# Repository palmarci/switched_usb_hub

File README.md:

# switched_usb_hub

a very cheap and basic switched usb 2.0 hub design based on:

- SL2.1A USB 4 way hub IC
- CH340C USB - serial adapter
- STM32F030F4Px microcontroller

the mcu talks with the PC over UART and toggles some FETs using GPIOs. nothing fancy.

original idea to use the SL2.1A: https://github.com/Hugoyhu/ZephyrHub/

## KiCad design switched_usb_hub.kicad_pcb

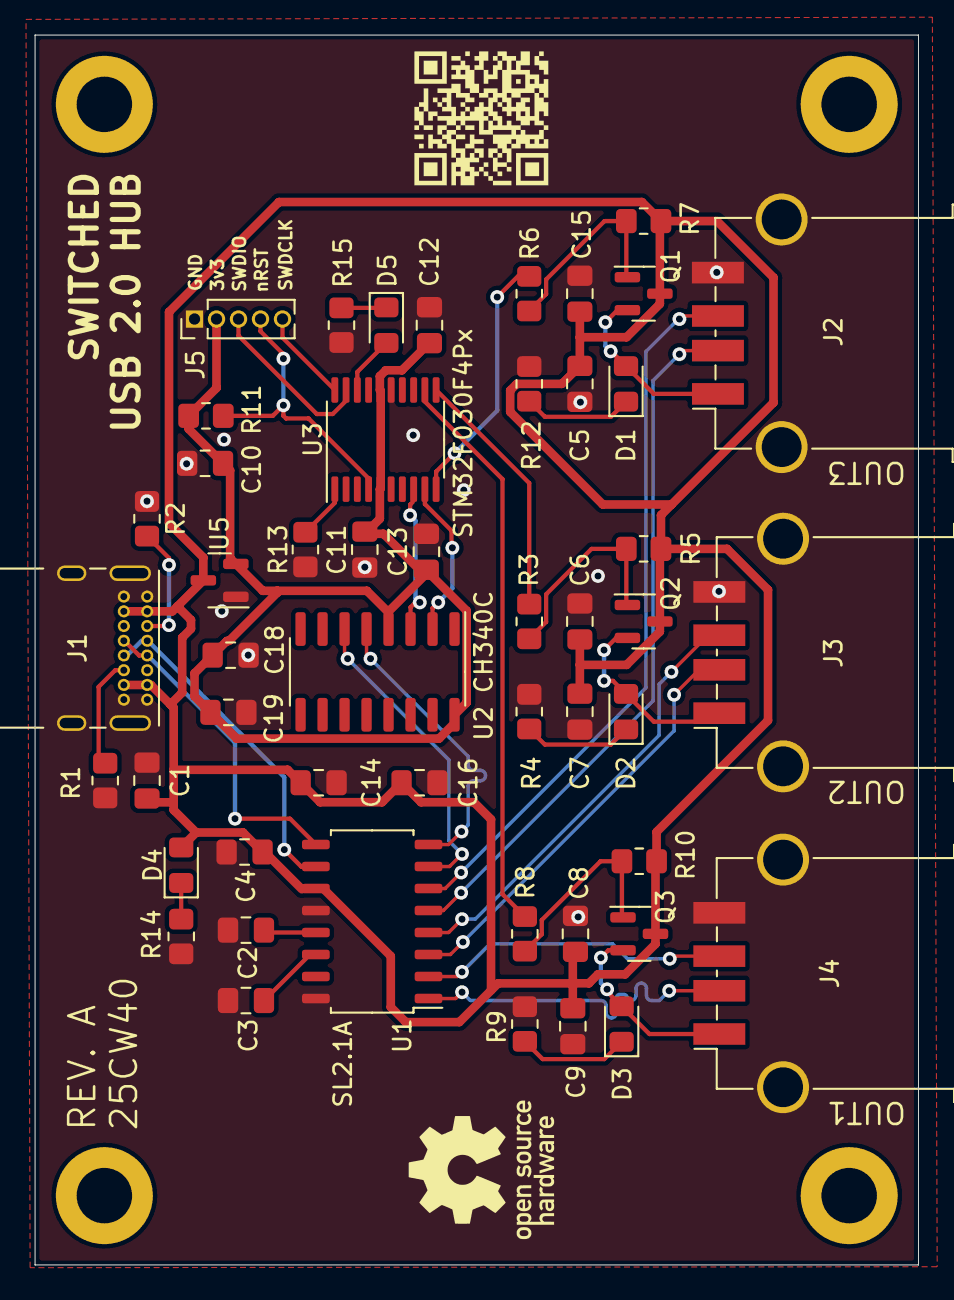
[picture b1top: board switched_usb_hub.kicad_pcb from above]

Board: 2 copper layers, 51.0 x 71.0 mm, 50 parts (0 on the bottom side), 38 nets.

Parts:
C1, C2, C3, C12, C14, C18: 10uF; C_0805_2012Metric_Pad1.18x1.45mm_HandSolder
C4, C6, C8, C10, C15, C16, C19: 100nF; C_0805_2012Metric_Pad1.18x1.45mm_HandSolder
C5, C7, C9, C11: 1uF; C_0805_2012Metric_Pad1.18x1.45mm_HandSolder
C13: 0.1uF; C_0805_2012Metric_Pad1.18x1.45mm_HandSolder
D1, D2, D3: LED; LED_0805_2012Metric_Pad1.15x1.40mm_HandSolder
D4: 5V IN; LED_0805_2012Metric_Pad1.15x1.40mm_HandSolder
D5: TEST LED; LED_0805_2012Metric_Pad1.15x1.40mm_HandSolder
J1: USB_C_Receptacle_USB2.0; USB_C_Receptacle_GCT_USB4085
J2, J3, J4: USB_A; USB_A_TE_292303-7_Horizontal
J5: JTAG_CONN; PinHeader_1x05_P1.27mm_Vertical
Q1, Q2, Q3: IRLML6402; SOT-23
R1, R2: 5.1K; R_0805_2012Metric_Pad1.20x1.40mm_HandSolder
R3, R6, R8: 100; R_0805_2012Metric_Pad1.20x1.40mm_HandSolder
R4, R9, R12, R14, R15: 330R; R_0805_2012Metric_Pad1.20x1.40mm_HandSolder
R5, R7, R10, R11, R13: 10k; R_0805_2012Metric_Pad1.20x1.40mm_HandSolder
U1: SL2.1A; SOIC-16_4.55x10.3mm_P1.27mm
U2: CH340C; SOIC-16_3.9x9.9mm_P1.27mm
U3: STM32F030F4Px; TSSOP-20_4.4x6.5mm_P0.65mm
U5: MCP1700x-330xxTT; SOT-23

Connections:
+3V3: C10.2, C11.2, C12.1, C13.1, C18.1, C19.1, J5.2 (VCC), R11.1, U2.4 (V3), U2.16 (VCC), U3.5 (VDDA), U3.16 (VDD), U5.2 (VO)
+5V: C1.1, C4.2, C5.1, C6.1, C7.1, C8.1, C9.1, C14.1, C15.1, C16.1, D4.2 (A), J1.A4 (VBUS), J1.A9 (VBUS), J1.B4 (VBUS), J1.B9 (VBUS), Q1.3 (D), Q2.3 (D), Q3.3 (D), R5.1, R7.1, R10.1, U1.11 (VCC5V), U5.3 (VI)
/D1+: U1.8 (DP1), U2.5 (UD+)
/D1-: U1.7 (DM1), U2.6 (UD-)
/D2+: J2.3 (D+), U1.6 (DP2)
/D2-: J2.2 (D-), U1.5 (DM2)
/D3+: J3.3 (D+), U1.4 (DP3)
/D3-: J3.2 (D-), U1.3 (DM3)
/D4+: J4.3 (D+), U1.2 (DP4)
/D4-: J4.2 (D-), U1.1 (DM4)
/mcu_subsys/PSU_SW0: R6.2, U3.10 (PA4)
/mcu_subsys/PSU_SW1: R3.2, U3.11 (PA5)
/mcu_subsys/PSU_SW2: R8.2, U3.12 (PA6)
GND: C1.2, C2.2, C3.1, C4.1, C5.2, C6.2, C7.2, C8.2, C9.2, C10.1, C11.1, C12.2, C13.2, C14.2, C15.2, C16.2, C18.2, C19.2, J1.A1 (GND), J1.A12 (GND), J1.B1 (GND), J1.B12 (GND), J1.S1 (SHIELD), J2.4 (GND), J2.5 (Shield), J3.4 (GND), J3.5 (Shield), J4.4 (GND), J4.5 (Shield), J5.1 (GND), R1.2, R2.1, R4.2, R9.2, R12.2, R13.1, R14.2, R15.2, U1.12 (GND), U1.16 (XIN), U3.15 (VSS), U5.1 (GND)
unnamed: C2.1, U1.13 (VDD3)
unnamed: C3.2, U1.14 (VDD18)
unnamed: D1.1 (K), R12.1
unnamed: D1.2 (A), J2.1 (VBUS), Q1.2 (S)
unnamed: D2.1 (K), R4.1
unnamed: D2.2 (A), J3.1 (VBUS), Q2.2 (S)
unnamed: D3.1 (K), R9.1
unnamed: D3.2 (A), J4.1 (VBUS), Q3.2 (S)
unnamed: D4.1 (K), R14.1
unnamed: D5.1 (K), R15.1
unnamed: D5.2 (A), U3.18 (PA10)
unnamed: J1.A5 (CC1), R2.2
unnamed: J1.A6 (D+), J1.B6 (D+), U1.10 (UDP)
unnamed: J1.A7 (D-), J1.B7 (D-), U1.9 (UDM)
unnamed: J1.B5 (CC2), R1.1
unnamed: J5.3 (SWDIO), U3.19 (PA13)
unnamed: J5.4 (nRST), R11.2, U3.4 (NRST)
unnamed: J5.5 (SWDCLK), U3.20 (PA14)
unnamed: Q1.1 (G), R6.1, R7.2
unnamed: Q2.1 (G), R3.1, R5.2
unnamed: Q3.1 (G), R8.1, R10.2
unnamed: R13.2, U3.1 (BOOT0)
unnamed: U2.2 (TXD), U3.9 (PA3)
unnamed: U2.3 (RXD), U3.8 (PA2)

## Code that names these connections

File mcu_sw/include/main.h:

#ifndef MAIN_H
#define MAIN_H

#include "stm32f030x6.h"
#include <stm32f0xx.h>
#include <stm32f0xx_hal.h>

#define PIN_TEST_LED    GPIO_PIN_10     // PA10
#define PIN_PSU_SW0     GPIO_PIN_4      // PA4
#define PIN_PSU_SW1     GPIO_PIN_5      // PA5
#define PIN_PSU_SW2     GPIO_PIN_6      // PA6
#define PIN_UART_TX     GPIO_PIN_2      // PA2
#define PIN_UART_RX     GPIO_PIN_3      // PA3

#define RX_BUF_SIZE     32

void SystemClock_Config(void);
void MX_GPIO_Init(void);
void MX_USART1_UART_Init(void);

extern int atoi (const char * str);

#endif // MAIN_H

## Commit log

2025-10-06 adding files
2025-10-06 adding rev A hopefully final files
2025-10-06 adding placeholder mcu sw project
2025-10-06 moving images
2025-10-07 wrote (untested) firmware
2025-10-07 oops wrong uart pin config
